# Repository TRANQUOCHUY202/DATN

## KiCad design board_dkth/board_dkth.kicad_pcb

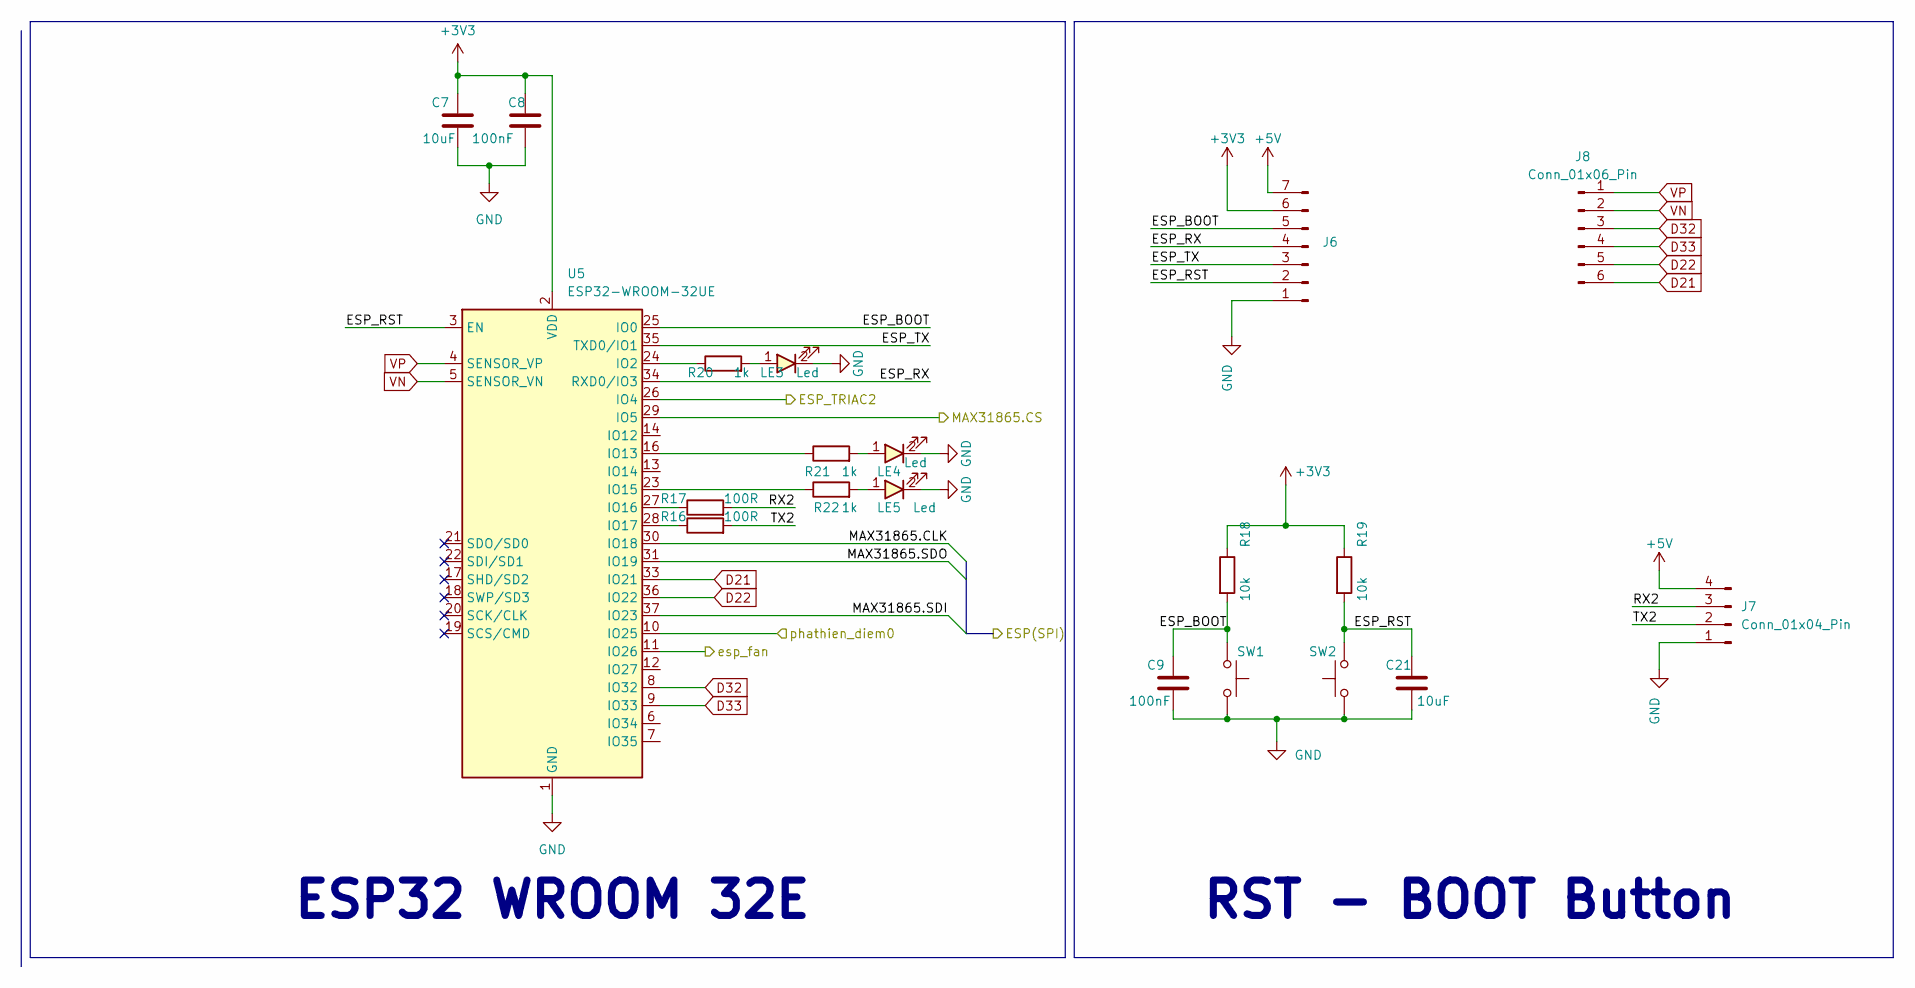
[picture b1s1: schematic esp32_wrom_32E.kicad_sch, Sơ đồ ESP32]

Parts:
C7, C21: 10uF; C_0603
C8, C9: 100nF; C_0603
J6: Conn_01x07_Pin; PinHeader_1x07_P2.54mm_Vertical
J7: Conn_01x04_Pin; PinHeader_1x04_P2.54mm_Vertical
J8: Conn_01x06_Pin; TerminalBlock_Phoenix_PT-1,5-6-5.0-H_1x06_P5.00mm_Horizontal
LE3, LE4, LE5: Led; LED_0603
R16, R17: 100R; R_0603
R18, R19: 10k; R_0603
R20, R21, R22: 1k; R_0603
SW1, SW2: SW_Push; SW_PUSH_6mm_H4.3mm
U5: ESP32-WROOM-32UE; ESP32-WROOM-32D

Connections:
+3.3V: C7.1, C8.1, J6.6, R18.1, R19.1, U5.2 (VDD); also elsewhere on the board
+5V: J6.7, J7.4; also elsewhere on the board
/esp32/ESP_BOOT: C9.1, J6.5, R18.2, SW1.1, U5.25 (IO0)
/esp32/ESP_RST: C21.1, J6.2, R19.2, SW2.2, U5.3 (EN)
/esp32/ESP_RX: J6.4, U5.34 (RXD0/IO3)
/esp32/ESP_TRIAC2: U5.26 (IO4); also elsewhere on the board
/esp32/ESP_TX: J6.3, U5.35 (TXD0/IO1)
/esp32/MAX31865.CLK: U5.30 (IO18)
/esp32/MAX31865.CS: U5.29 (IO5); also elsewhere on the board
/esp32/MAX31865.SDI: U5.37 (IO23)
/esp32/MAX31865.SDO: U5.31 (IO19)
/esp32/RX2: J7.3, R17.2
/esp32/TX2: J7.2, R16.2
/esp32/esp_fan: U5.11 (IO26); also elsewhere on the board
/esp32/phathien_diem0: U5.10 (IO25); also elsewhere on the board
D21: J8.6, U5.33 (IO21)
D22: J8.5, U5.36 (IO22)
D32: J8.3, U5.8 (IO32)
D33: J8.4, U5.9 (IO33)
GND: C7.2, C8.2, C9.2, C21.2, J6.1, J7.1, LE3.2, LE4.2, LE5.2, SW1.2, SW2.1, U5.1 (GND), U5.15 (GND), U5.38 (GND), U5.39 (GND); also elsewhere on the board
unnamed: LE3.1, R20.2
unnamed: LE4.1, R21.2
unnamed: LE5.1, R22.2
unnamed: R20.1, U5.24 (IO2)
unnamed: R21.1, U5.16 (IO13)
unnamed: R22.1, U5.23 (IO15)
unnamed: R17.1, U5.27 (IO16)
unnamed: R16.1, U5.28 (IO17)
VN: J8.2, U5.5 (SENSOR_VN)
VP: J8.1, U5.4 (SENSOR_VP)

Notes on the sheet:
ESP32 WROOM 32E
RST - BOOT Button

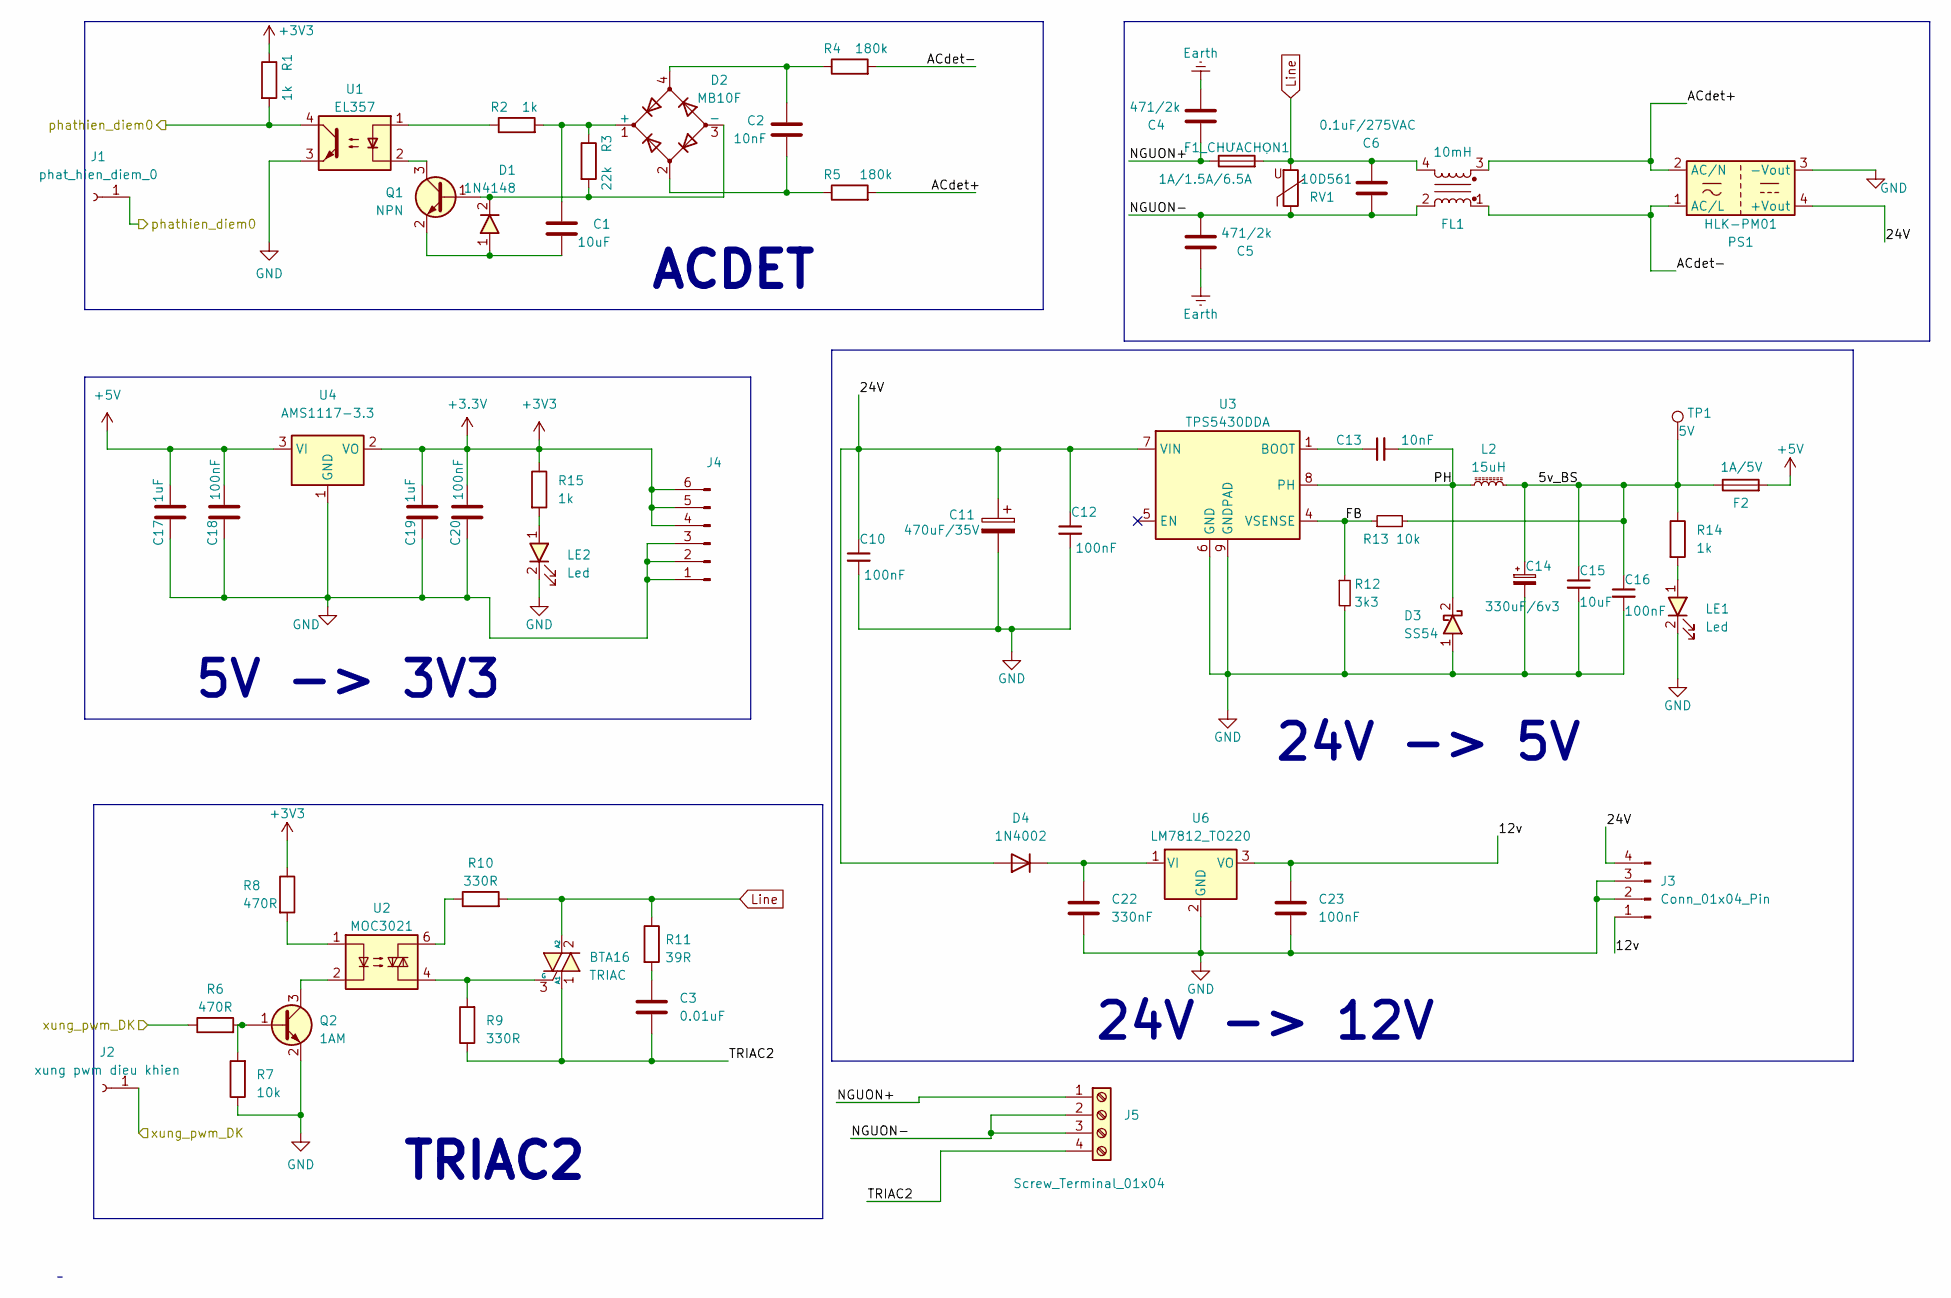
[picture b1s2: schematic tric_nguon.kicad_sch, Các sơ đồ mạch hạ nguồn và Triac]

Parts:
BTA16: TRIAC; TO-220-3_Vertical_heatsink_cutBoard
C1, C15: 10uF; C_0603
C2: 10nF; C_0805
C3: 0.01uF; C_Disc_D12.5mm_W5.0mm_P10.00mm
C4, C5: 471/2k; C_Disc_D4.3mm_W1.9mm_P5.00mm
C6: 0.1uF/275VAC; C_Rect_L16.5mm_W5.0mm_P15.00mm_MKT
C10, C12, C16, C18, C20, C23: 100nF; C_0603
C11: 470uF/35V; CP_Alu_SMD_10x10.5mm
C13: 10nF; C_0603
C14: 330uF/6v3; CP_Alu_SMD_6.3x7.7mm
C17, C19: 1uF; C_0603
C22: 330nF; C_0603
D1: 1N4148; D_SOD323
D2: MB10F; Bridge_MB10F-13
D3: SS54; Package-Diode-D_SMA
D4: 1N4002; D_DO-41_SOD81_P10.16mm_Horizontal
F1_CHƯACHỌN1: 1A/1.5A/6.5A; Fuse_HolderGlass5x20mm
F2: 1A/5V; Fuse_1812_4532Metric
FL1: 10mH; ACFilterChoke-UU9.8
J1: phat_hien_diem_0; PinHeader_1x01_P2.54mm_Vertical
J2: xung pwm dieu khien; PinHeader_1x01_P2.54mm_Vertical
J3: Conn_01x04_Pin; TerminalBlock_Phoenix_PT-1,5-4-5.0-H_1x04_P5.00mm_Horizontal
J4: Conn_01x06_Pin; PinHeader_1x06_P2.54mm_Vertical
J5: Screw_Terminal_01x04; TerminalBlock_Screw_HB9500_4P_P9.5mm
L2: 15uH; L_6.6x6.6
LE1, LE2: Led; LED_0603
PS1: HLK-PM01; PowerSuppy-ACDC-HLK_P01
Q1: NPN; SOT23-3
Q2: 1AM; SOT23-3
R1, R2, R14, R15: 1k; R_0603
R3: 22k; R_0603
R4, R5: 180k; R_0805
R6, R8: 470R; R_0603
R7, R13: 10k; R_0603
R9, R10: 330R; R_2512
R11: 39R; R_Axial_DIN0414_L11.9mm_D4.5mm_P5.08mm_Vertical
R12: 3k3; R_0603
RV1: 10D561; Varistor-RV-Disc-D12mm-W3.9mm-P7.5mm
TP1: 5V; TestPoint_Pad_D1.0mm
U1: EL357; OPTO_EL357N-G
U2: MOC3021; DIL06-SMD
U3: TPS5430DDA; SOIC8E(EXPOSED PAD)
U4: AMS1117-3.3; SOT-223-3_TabPin2
U6: LM7812_TO220; TO-220-3_Vertical

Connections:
+3.3V: C19.2, C20.2, J4.4, J4.5, J4.6, R1.1, R8.1, R15.1, U4.2 (VO); also elsewhere on the board
+5V: C17.2, C18.2, F2.2, U4.3 (VI); also elsewhere on the board
/5v_BS: C14.1, C15.1, C16.1, F2.1, L2.2, R13.2, R14.1, TP1.1
/FB: R12.1, R13.1, U3.4 (VSENSE)
/NGUON+: C4.1, F1_CHƯACHỌN1.1, J5.1
/PH: C13.2, D3.2, L2.1, U3.8 (PH)
/esp32/ESP_TRIAC2: J2.1, R6.1; also elsewhere on the board
/esp32/phathien_diem0: J1.1, R1.2, U1.4; also elsewhere on the board
/triac+nguon/12v: C23.1, J3.1, U6.3 (VO)
/triac+nguon/24V: C10.1, C11.1, C12.1, D4.2 (A), J3.4, PS1.4 (+Vout), U3.7 (VIN)
/triac+nguon/ACdet+: FL1.3, PS1.2 (AC/N), R5.2
/triac+nguon/ACdet-: FL1.1, PS1.1 (AC/L), R4.2
/triac+nguon/NGUON-: C5.2, C6.1, FL1.2, J5.2, J5.3, RV1.1
/triac+nguon/TRIAC2: BTA16.1 (A1), C3.2, J5.4, R9.1
Earth: C4.2, C5.1
GND: C10.2, C11.2, C12.2, C14.2, C15.2, C16.2, C17.1, C18.1, C19.1, C20.1, C22.2, C23.2, D3.1, J3.2, J3.3, J4.1, J4.2, J4.3, LE1.2, LE2.2, PS1.3 (-Vout), Q2.2 (E), R7.1, R12.2, U1.3, U3.6 (GND), U3.9 (GNDPAD), U4.1 (GND), U6.2 (GND); also elsewhere on the board
Line: BTA16.2 (A2), C6.2, F1_CHƯACHỌN1.2, FL1.4, R10.2, R11.1, RV1.2
unnamed: BTA16.3 (G), R9.2, U2.4
unnamed: C2.1, D2.4, R4.1
unnamed: C2.2, D2.2, R5.1
unnamed: C3.1, R11.2
unnamed: C1.1, D2.1 (+), R2.2, R3.1
unnamed: D1.2, D2.3 (-), Q1.1 (B), R3.2
unnamed: C22.1, D4.1 (K), U6.1 (VI)
unnamed: LE1.1, R14.2
unnamed: LE2.1, R15.2
unnamed: Q1.3 (C), U1.2
unnamed: C1.2, D1.1, Q1.2 (E)
unnamed: Q2.1 (B), R6.2, R7.2
unnamed: Q2.3 (C), U2.2
unnamed: R2.1, U1.1
unnamed: R8.2, U2.1
unnamed: R10.1, U2.6
unnamed: C13.1, U3.1 (BOOT)

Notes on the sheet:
ACDET
5V -> 3V3
24V -> 5V
24V -> 12V
TRIAC2

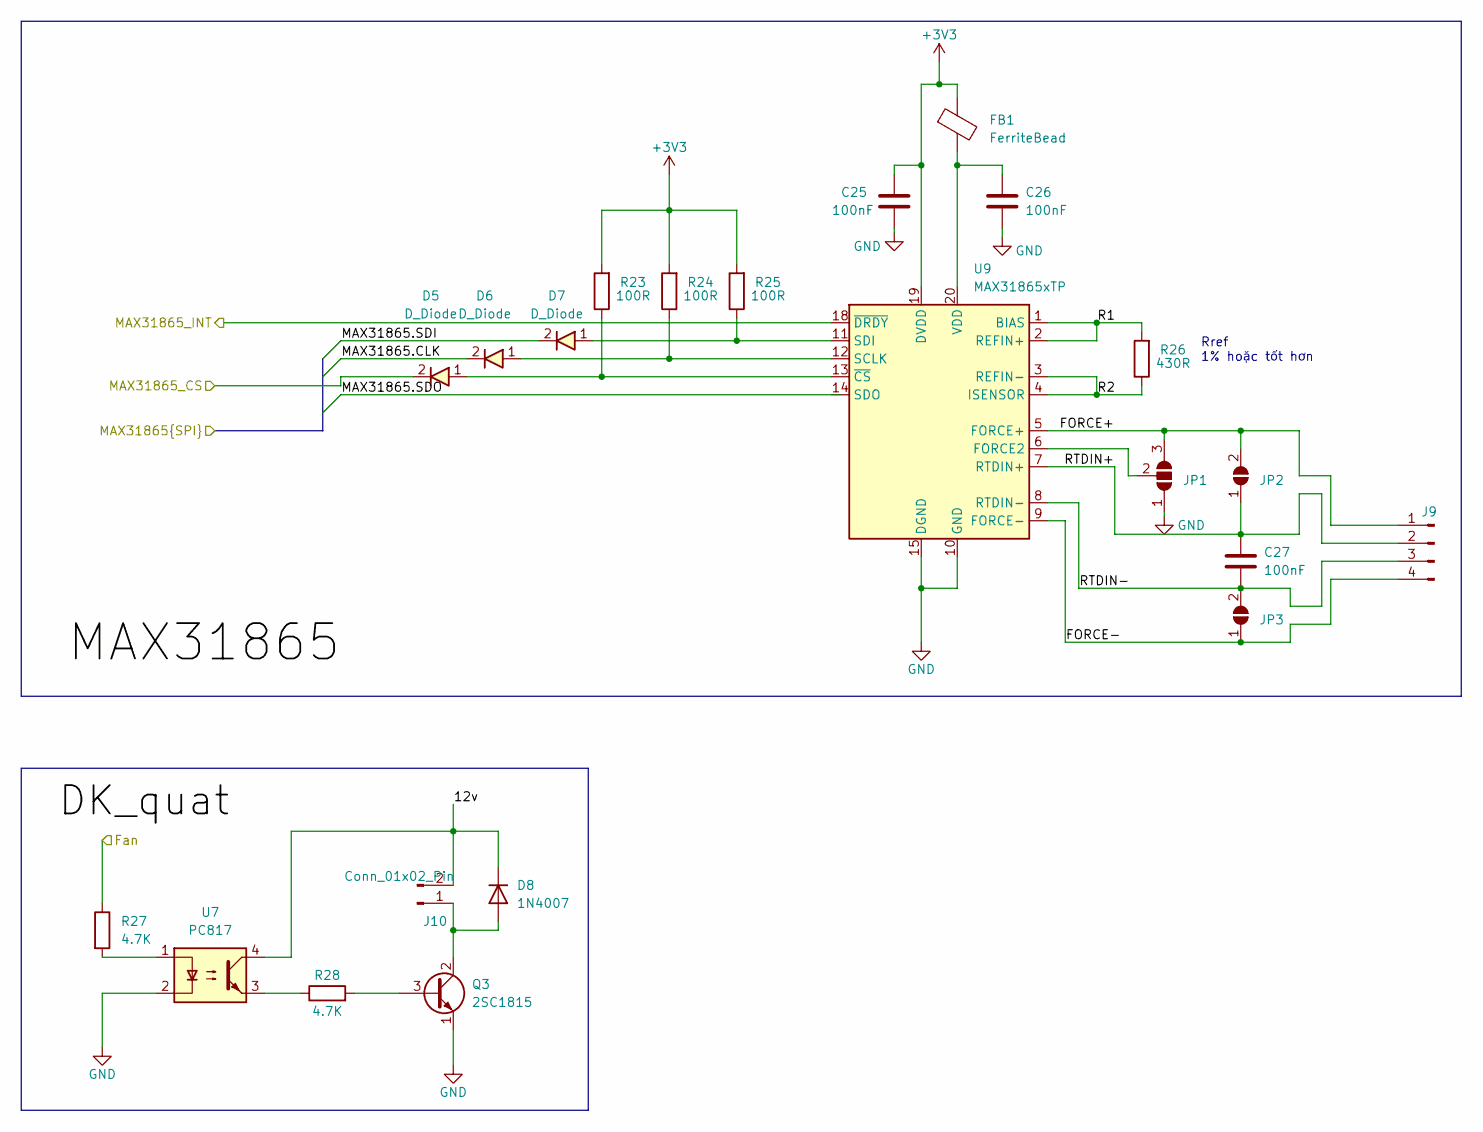
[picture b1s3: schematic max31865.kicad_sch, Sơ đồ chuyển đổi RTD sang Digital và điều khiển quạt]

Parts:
C25, C26, C27: 100nF; C_0603
D5, D6, D7: D_Diode; Package-Diode-D_SOD_323
D8: 1N4007; D_DO-41_SOD81_P10.16mm_Horizontal
FB1: FerriteBead; R_0805
J9: Conn_01x04_Pin; TerminalBlock_Phoenix_PT-1,5-4-5.0-H_1x04_P5.00mm_Horizontal
J10: Conn_01x02_Pin; TerminalBlock_Phoenix_PT-1,5-2-5.0-H_1x02_P5.00mm_Horizontal
JP1: SolderJumper_3_Open; SolderJumper-3_P1.3mm_Bridged12_RoundedPad1.0x1.5mm
JP2, JP3: SolderJumper_2_Open; SolderJumper-2_P1.3mm_Open_RoundedPad1.0x1.5mm
Q3: 2SC1815; TO-92_Inline
R23, R24, R25: 100R; R_0603
R26: 430R; R_0805
R27, R28: 4.7K; R_0805
U7: PC817; DIP-4_W7.62mm
U9: MAX31865xTP; TQFN-20-1EP_5x5mm_P0.65mm_EP3.25x3.25mm

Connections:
+3.3V: C25.1, FB1.1, R23.2, R24.2, R25.2, U9.19 (DVDD); also elsewhere on the board
/esp32/MAX31865.CS: D5.2; also elsewhere on the board
/esp32/esp_fan: R27.1; also elsewhere on the board
/max31865/12v: D8.1 (K), J10.2, U7.4
/max31865/FORCE+: J9.1, JP1.3 (B), JP2.2 (B), U9.5 (FORCE+)
/max31865/FORCE-: J9.4, JP3.1 (A), U9.9 (FORCE-)
/max31865/MAX31865.CLK: D6.2
/max31865/MAX31865.SDI: D7.2
/max31865/MAX31865_INT: U9.18 (~DRDY)
/max31865/R1: R26.2, U9.1 (BIAS), U9.2 (REFIN+)
/max31865/R2: R26.1, U9.3 (REFIN-), U9.4 (ISENSOR)
/max31865/RTDIN+: C27.1, J9.2, JP2.1 (A), U9.7 (RTDIN+)
/max31865/RTDIN-: C27.2, J9.3, JP3.2 (B), U9.8 (RTDIN-)
GND: C25.2, C26.2, JP1.1 (A), Q3.1 (E), U7.2, U9.10 (GND), U9.15 (DGND), U9.16 (GND), U9.21 (GND); also elsewhere on the board
unnamed: D8.2 (A), J10.1, Q3.2 (C)
unnamed: JP1.2 (C), U9.6 (FORCE2)
unnamed: Q3.3 (B), R28.2
unnamed: R27.2, U7.1
unnamed: R28.1, U7.3
unnamed: D6.1, R24.1, U9.12 (SCLK)
unnamed: D7.1, R25.1, U9.11 (SDI)
unnamed: C26.1, FB1.2, U9.20 (VDD)
unnamed: D5.1, R23.1, U9.13 (~CS)

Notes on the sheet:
Rref 1% hoặc tốt hơn

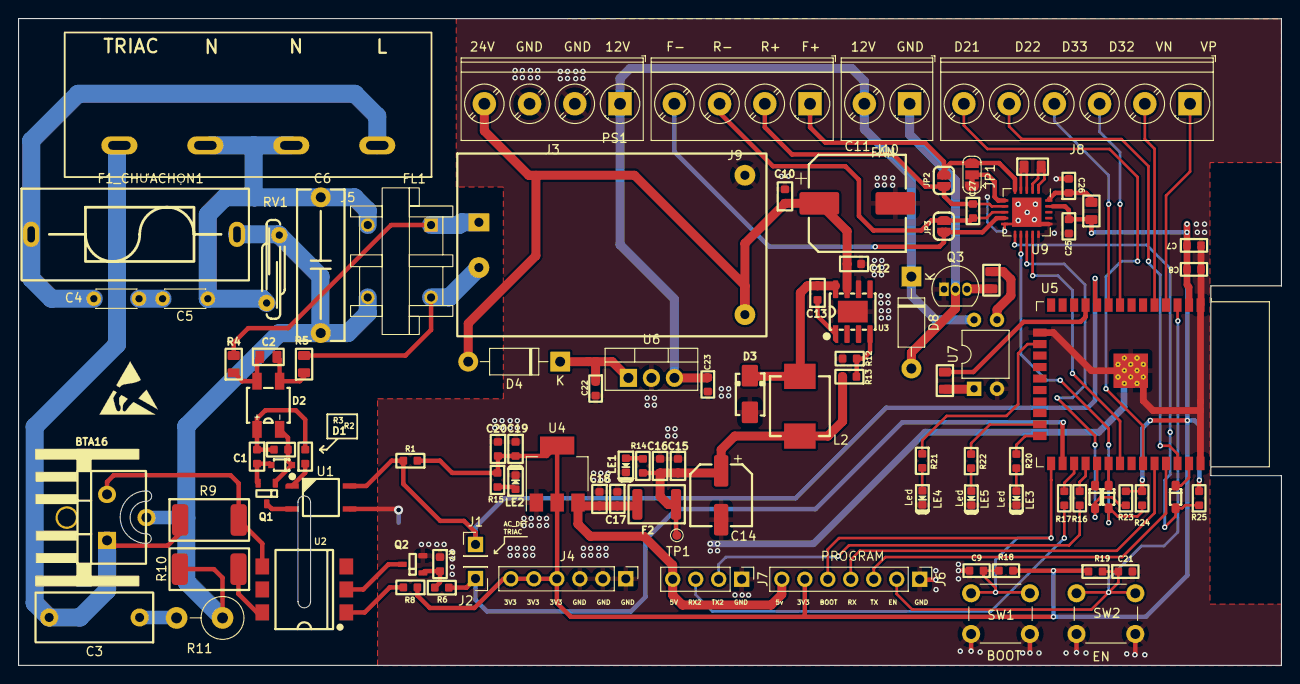
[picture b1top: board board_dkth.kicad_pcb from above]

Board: 2 copper layers, 139.6 x 71.5 mm, 102 parts (0 on the bottom side), 72 nets.

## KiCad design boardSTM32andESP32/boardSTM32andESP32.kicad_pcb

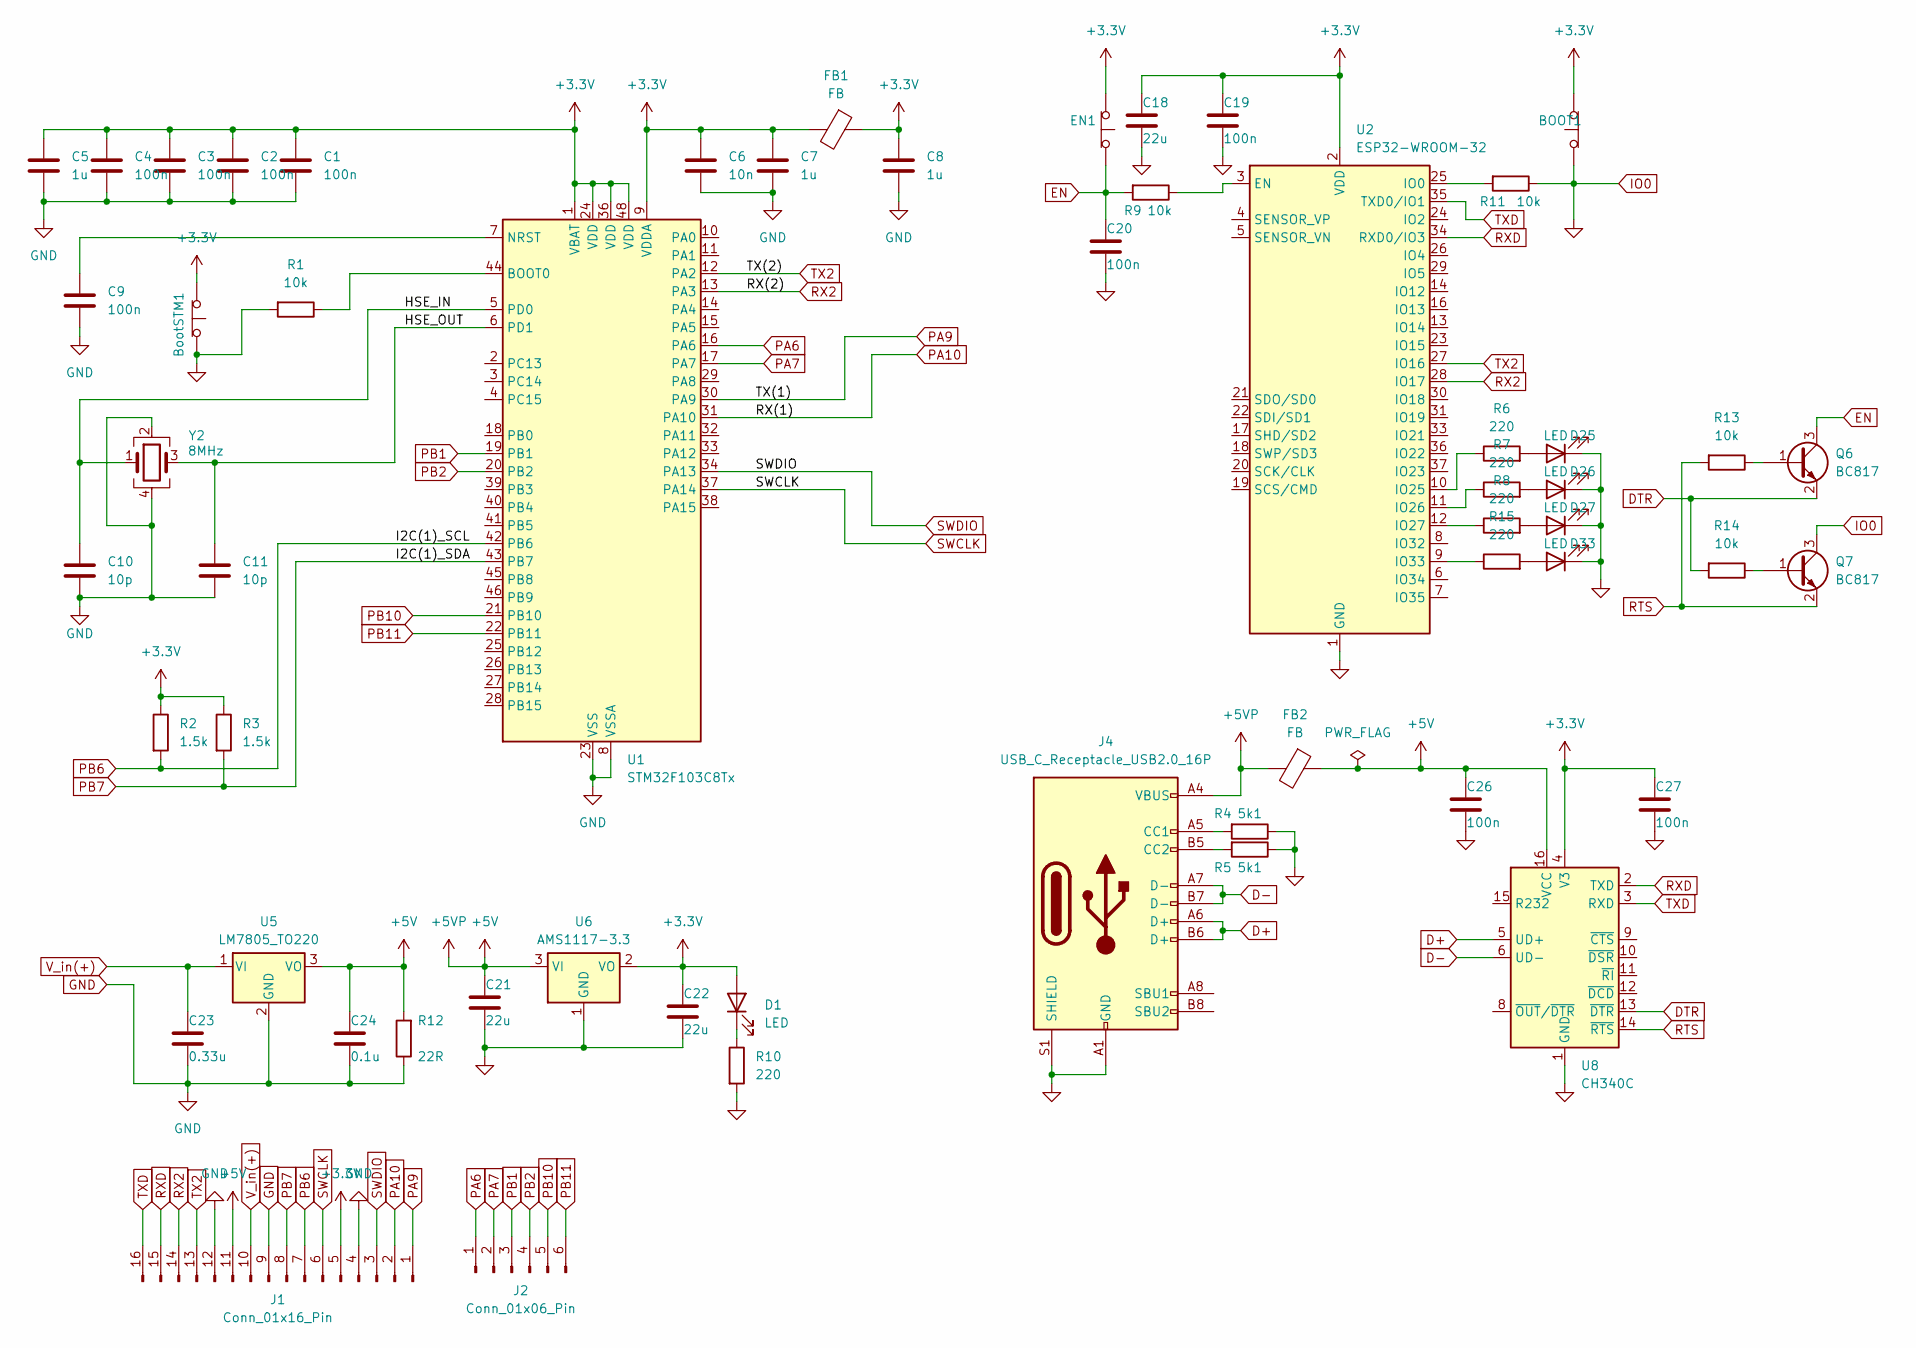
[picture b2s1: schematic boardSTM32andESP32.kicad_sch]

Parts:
BOOT1: SW_PUSH_6mm_H4.3mm
BootSTM1: SW_PUSH_6mm_H4.3mm
C1, C2, C3, C4, C9, C19, C20, C26, C27: 100n; C_1206_3216Metric
C5, C7, C8: 1u; C_0805_2012Metric
C6: 10n; C_0805_2012Metric
C10, C11: 10p; C_1206_3216Metric
C18, C21, C22: 22u; C_1206_3216Metric
C23: 0.33u; C_1206_3216Metric
C24: 0.1u; C_1206_3216Metric
D1, D25, D26, D27, D33: LED; LED_0805_2012Metric
EN1: SW_PUSH_6mm_H4.3mm
FB1, FB2: FB; L_0805_2012Metric
J1: Conn_01x16_Pin; TerminalBlock_Phoenix_PT-1,5-16-5.0-H_1x16_P5.00mm_Horizont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
J2: Conn_01x06_Pin; TerminalBlock_Phoenix_PT-1,5-6-5.0-H_1x06_P5.00mm_Horizontal
J4: USB_C_Receptacle_USB2.0_16P; USB_C_Receptacle_HCTL_HC-TYPE-C-16P-01A
Q6, Q7: BC817; SOT-23
R1, R9, R11, R13, R14: 10k; R_1206_3216Metric
R2, R3: 1.5k; R_1206_3216Metric
R4, R5: 5k1; R_1206_3216Metric
R6, R7, R8, R10, R15: 220; R_1206_3216Metric
R12: 22R; R_1206_3216Metric
U1: STM32F103C8Tx; LQFP-48_7x7mm_P0.5mm
U2: ESP32-WROOM-32
U5: LM7805_TO220; TO-220-3_Vertical
U6: AMS1117-3.3; SOT-223-3_TabPin2
U8: CH340C; SOP-16_3.9x9.9mm_P1.27mm
Y2: 8MHz; Crystal_SMD_5032-4Pin_5.0x3.2mm

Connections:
+3.3V: BOOT1.2 (B), BootSTM1.2 (B), C1.1, C2.1, C3.1, C4.1, C5.1, C6.1, C7.1, C8.1, C18.1, C19.1, C22.1, C27.1, D1.2 (A), EN1.2 (B), FB1.1, FB1.2, J1.5, R2.1, R3.1, U1.1 (VBAT), U1.9 (VDDA), U1.24 (VDD), U1.36 (VDD), U1.48 (VDD), U2.2 (VDD), U6.2 (VO), U8.4 (V3)
+5V: C21.1, C24.1, C26.1, FB2.1, FB2.2, J1.11, J4.A4 (VBUS), J4.A9 (VBUS), J4.B4 (VBUS), J4.B9 (VBUS), R12.2, U5.3 (VO), U6.3 (VI), U8.16 (VCC)
/HSE_IN: C10.1, U1.5 (PD0), Y2.1
/HSE_OUT: C11.1, U1.6 (PD1), Y2.3
D+: J4.A6 (D+), J4.B6 (D+), U8.5 (UD+)
D-: J4.A7 (D-), J4.B7 (D-), U8.6 (UD-)
DTR: Q6.2 (E), R14.2, U8.13 (~DTR)
EN: C20.1, EN1.1 (A), Q6.3 (C), R9.2
GND: BOOT1.1 (A), BootSTM1.1 (A), C1.2, C2.2, C3.2, C4.2, C5.2, C6.2, C7.2, C8.2, C9.2, C10.2, C11.2, C18.2, C19.2, C20.2, C21.2, C22.2, C23.2, C24.2, C26.2, C27.2, D25.1 (K), D26.1 (K), D27.1 (K), D33.1 (K), J1.4, J1.9, J1.12, J4.A1 (GND), J4.A12 (GND), J4.B1 (GND), J4.B12 (GND), J4.S1 (SHIELD), Q7.3 (C), R1.2, R4.1, R5.1, R10.2, R11.1, R12.1, U1.8 (VSSA), U1.23 (VSS), U1.35 (VSS), U1.47 (VSS), U2.1 (GND), U2.15 (GND), U2.38 (GND), U2.39 (GND), U5.2 (GND), U6.1 (GND), U8.1 (GND), Y2.2, Y2.4
unnamed: D1.1 (K), R10.1
unnamed: D25.2 (A), R6.2
unnamed: D26.2 (A), R7.2
unnamed: D27.2 (A), R8.2
unnamed: D33.2 (A), R15.2
unnamed: J4.A5 (CC1), R4.2
unnamed: J4.B5 (CC2), R5.2
unnamed: Q6.1 (B), R13.1
unnamed: Q7.1 (B), R14.1
unnamed: R1.1, U1.44 (BOOT0)
unnamed: C9.1, U1.7 (NRST)
unnamed: R9.1, U2.3 (EN)
unnamed: R11.2, U2.25 (IO0)
unnamed: R6.1, U2.10 (IO25)
unnamed: R7.1, U2.11 (IO26)
unnamed: R8.1, U2.12 (IO27)
unnamed: R15.1, U2.9 (IO33)
PA6: J2.1, U1.16 (PA6)
PA7: J2.2, U1.17 (PA7)
PA9: J1.1, U1.30 (PA9)
PA10: J1.2, U1.31 (PA10)
PB1: J2.3, U1.19 (PB1)
PB2: J2.4, U1.20 (PB2)
PB6: J1.7, R2.2, U1.42 (PB6)
PB7: J1.8, R3.2, U1.43 (PB7)
PB10: J2.5, U1.21 (PB10)
PB11: J2.6, U1.22 (PB11)
RTS: Q7.2 (E), R13.2, U8.14 (~RTS)
RX2: J1.14, U1.13 (PA3), U2.28 (IO17)
RXD: J1.15, U2.34 (RXD0/IO3), U8.2 (TXD)
SWCLK: J1.6, U1.37 (PA14)
SWDIO: J1.3, U1.34 (PA13)
TX2: J1.13, U1.12 (PA2), U2.27 (IO16)
TXD: J1.16, U2.35 (TXD0/IO1), U8.3 (RXD)
V_in(+): C23.1, J1.10, U5.1 (VI)

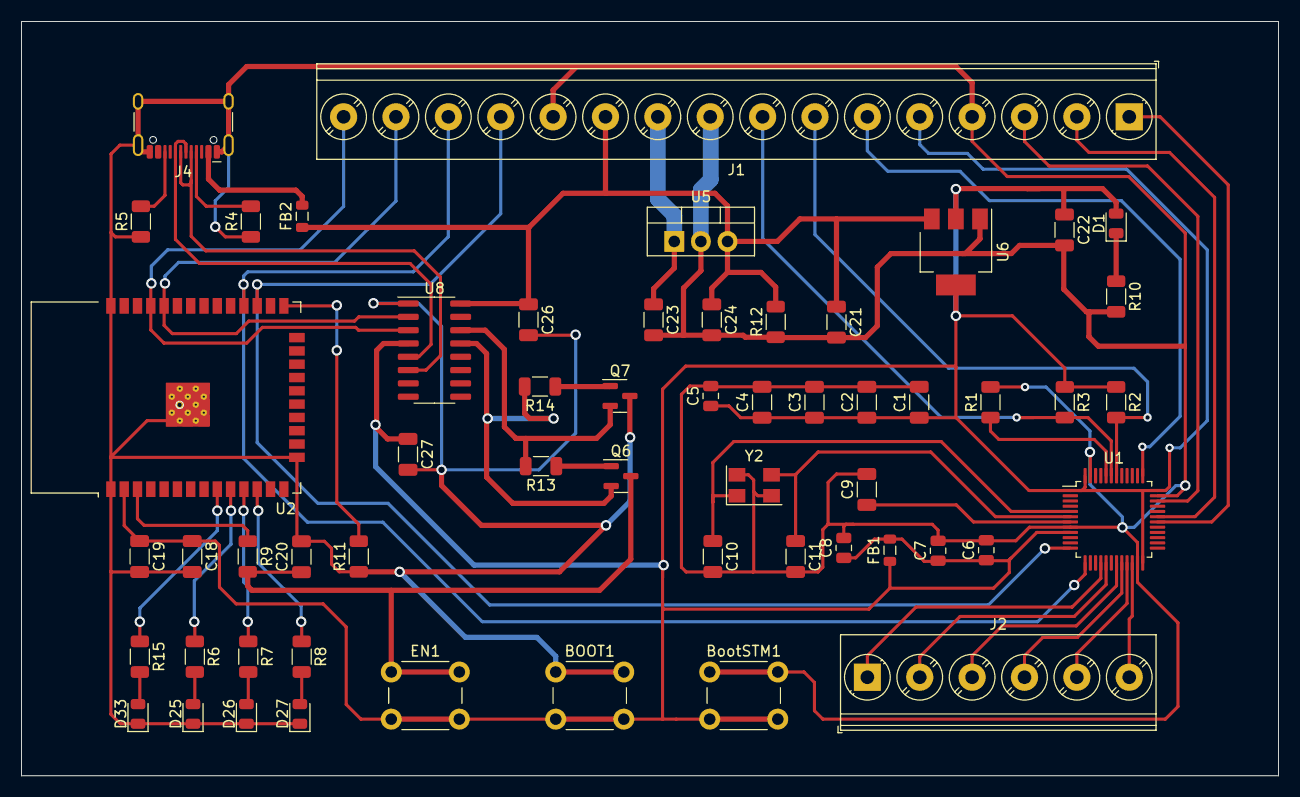
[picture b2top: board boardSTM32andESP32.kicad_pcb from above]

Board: 2 copper layers, 120.0 x 72.0 mm, 56 parts (0 on the bottom side), 44 nets.
